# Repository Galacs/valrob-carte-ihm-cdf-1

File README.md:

# Carte IHM CDF 1

ESP32-S3-WROOM-1 HM interface card

## IC List

- ESP32-S3-WROOM-1 (Main MCU Module)
- TLV757P (MCU 3v3 LDO)
- SSD1315 (128x64 OLED display)
- 3x WS2812B (RGB status leds)
- 74HC14 (HEX Schmitt trigger)

## Top preview

## Preview 3d render

## Pin definitions

```c
#define DIP_A_PIN 14
#define DIP_B_PIN 21
#define DIP_C_PIN 47
#define DIP_D_PIN 48

#define STARTER_PIN 11

#define TEAM_A_PIN 13
#define TEAM_B_PIN 12

#define UP_BTN_PIN 10
#define DOWN_BTN_PIN 17
#define CONF_BTN_PIN 18

#define OLED_I2C_SCL 3
#define OLED_I2C_SDA 9

#define RBG_LEDS_PIN 45

#define BATT_SENSE_PIN 2
```

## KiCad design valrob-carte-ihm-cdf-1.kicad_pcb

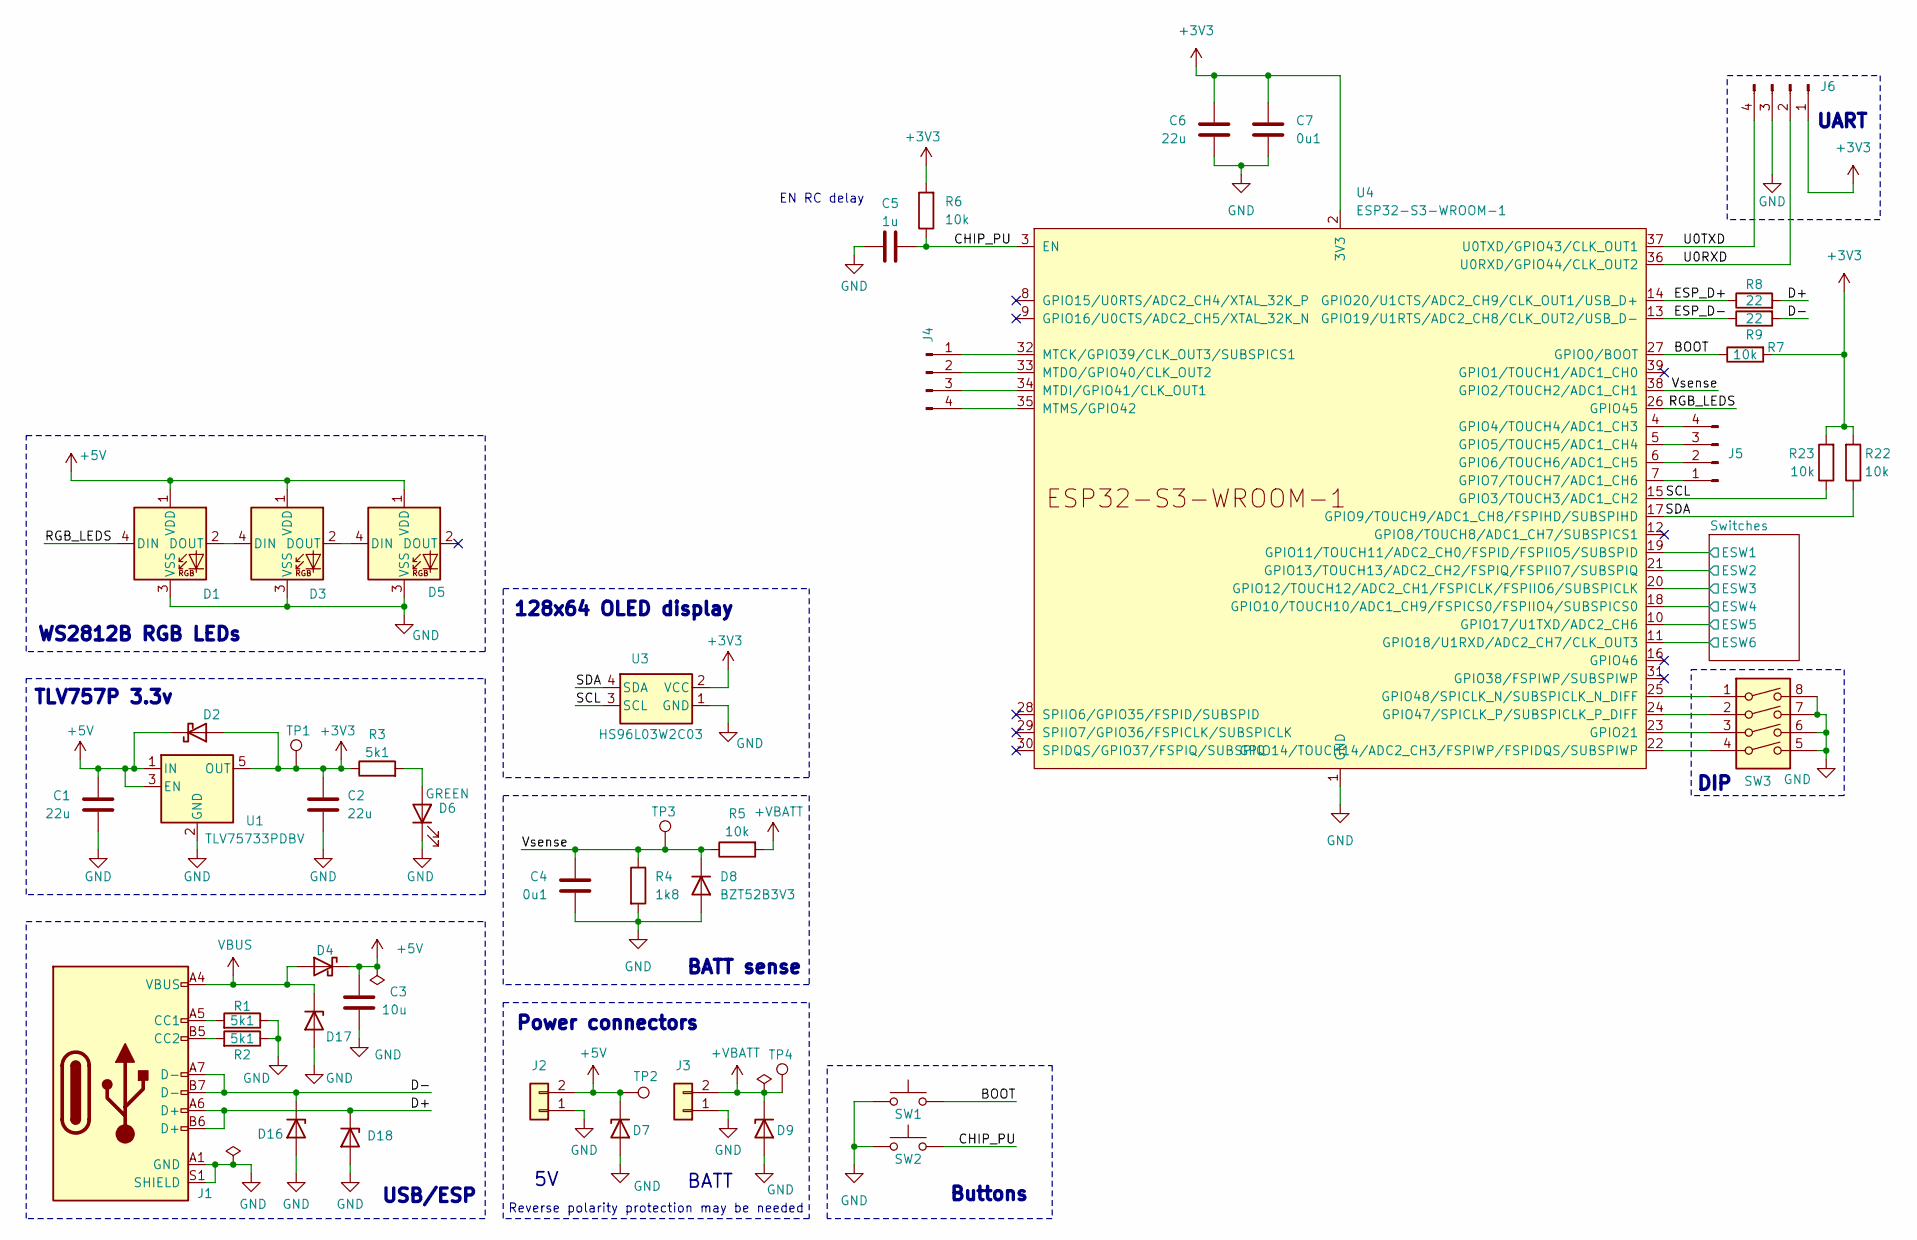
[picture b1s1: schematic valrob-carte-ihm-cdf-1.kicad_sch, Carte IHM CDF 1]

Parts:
C1, C2, C6: 22u; C_0603_1608Metric; Manufacturer Part Number CL10A226MQ8NRNC; JLCPCB Part # C59461
C3: 10u; C_0603_1608Metric; Manufacturer Part Number CL10A106KP8NNNC; JLCPCB Part # C19702
C4, C7: 0u1; C_0402_1005Metric; Manufacturer Part Number CL05B104KO5NNNC; JLCPCB Part # C1525
C5: 1u; C_0402_1005Metric; Manufacturer Part Number CL05A105KA5NQNC; JLCPCB Part # C52923
D1, D3, D5: WS2812B; LED_WS2812B_PLCC4_5.0x5.0mm_P3.2mm; Manufacturer Part Number WS2812B-HS01/W; JLCPCB Part # C22371521
D2, D4: D_Schottky; D_SMA; Manufacturer Part Number SS54; JLCPCB Part # C22452
D6: GREEN; LED_0805_2012Metric; Manufacturer Part Number KT-0805G; JLCPCB Part # C2297
D7: P6SMB6.8CA/TR13; D_SMB; Manufacturer Part Number P6SMB6.8CA/TR13; JLCPCB Part # C78395
D8: BZT52B3V3; D_SOD-123; Manufacturer Part Number BZT52B3V3; JLCPCB Part # C19077392
D9: SMAJ12A; D_SMA; Manufacturer Part Number SMAJ12A; JLCPCB Part # C19077531
D16, D17, D18: H5VU10U; Diode_DFN1006; Manufacturer Part Number H5VU10U; JLCPCB Part # C22395519
J1: USB_C_Receptacle_USB2.0_14P; USB_C_Receptacle_HRO_TYPE-C-31-M-12; Manufacturer Part Number TYPE-C16PIN; JLCPCB Part # C393939
J2, J3: Conn_01x02; JST_XH_S2B-XH-A_1x02_P2.50mm_Horizontal
J4, J5, J6: Conn_01x04_Pin; PinHeader_1x04_P2.54mm_Vertical
R1, R2, R3: 5k1; R_0402_1005Metric; Manufacturer Part Number 0402WGF5101TCE; JLCPCB Part # C25905
R4: 1k8; R_0603_1608Metric; Manufacturer Part Number 0603WAF1801T5E; JLCPCB Part # C4177
R5, R6, R7, R22, R23: 10k; R_0402_1005Metric; Manufacturer Part Number 0402WGF1002TCE; JLCPCB Part # C25744
R8, R9: 22; R_0402_1005Metric; Manufacturer Part Number 0402WGF220JTCE; JLCPCB Part # C25092
SW1, SW2: SW_Push; SW_SPST_TS-1088-xR020; Manufacturer Part Number TS-1088-AR02016; JLCPCB Part # C720477
SW3: SW_DIP_x04; SW_DIP_SPSTx04_Slide_9.78x12.34mm_W7.62mm_P2.54mm
TP1, TP2, TP3, TP4: TestPoint; TestPoint_Pad_D2.0mm
U1: TLV75733PDBV; SOT-23-5; Manufacturer Part Number TLV75733PDBVR; JLCPCB Part # C485517
U3: HS96L03W2C03
U4: ESP32-S3-WROOM-1

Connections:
+3V3: C2.2, C6.1, C7.1, D2.2 (A), J6.1, R3.1, R6.2, R7.2, R22.2, R23.2, TP1.1, U1.5 (OUT), U3.2 (VCC), U4.2 (3V3); also elsewhere on the board
+5V: C1.2, C3.1, D1.1 (VDD), D2.1 (K), D3.1 (VDD), D4.1 (K), D5.1 (VDD), D7.1 (K), J2.2, TP2.1, U1.1 (IN), U1.3 (EN)
+VBATT: D9.1 (K), J3.2, R5.2, TP4.1
/BOOT: R7.1, SW1.2, U4.27 (GPIO0/BOOT)
/CHIP_PU: C5.2, R6.1, SW2.2, U4.3 (EN)
/D+: D18.1 (K), J1.A6 (D+), J1.B6 (D+), R8.2
/D-: D16.1 (K), J1.A7 (D-), J1.B7 (D-), R9.2
/ESP_D+: R8.1, U4.14 (GPIO20/U1CTS/ADC2_CH9/CLK_OUT1/USB_D+)
/ESP_D-: R9.1, U4.13 (GPIO19/U1RTS/ADC2_CH8/CLK_OUT2/USB_D-)
/RGB_LEDS: D1.4 (DIN), U4.26 (GPIO45)
/SCL: R23.1, U3.3 (SCL), U4.15 (GPIO3/TOUCH3/ADC1_CH2)
/SDA: R22.1, U3.4 (SDA), U4.17 (GPIO9/TOUCH9/ADC1_CH8/FSPIHD/SUBSPIHD)
/Switches/ESW1: U4.19 (GPIO11/TOUCH11/ADC2_CH0/FSPID/FSPIIO5/S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); also elsewhere on the board
/Switches/ESW2: U4.21 (GPIO13/TOUCH13/ADC2_CH2/FSPIQ/FSPIIO7/S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); also elsewhere on the board
/Switches/ESW3: U4.20 (GPIO12/TOUCH12/ADC2_CH1/FSPICLK/FSPIIO6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); also elsewhere on the board
/Switches/ESW4: U4.18 (GPIO10/TOUCH10/ADC1_CH9/FSPICS0/FSPIIO4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); also elsewhere on the board
/Switches/ESW5: U4.10 (GPIO17/U1TXD/ADC2_CH6); also elsewhere on the board
/Switches/ESW6: U4.11 (GPIO18/U1RXD/ADC2_CH7/CLK_OUT3); also elsewhere on the board
/U0RXD: J6.2, U4.36 (U0RXD/GPIO44/CLK_OUT2)
/U0TXD: J6.4, U4.37 (U0TXD/GPIO43/CLK_OUT1)
/Vsense: C4.1, D8.1 (K), R4.1, R5.1, TP3.1, U4.38 (GPIO2/TOUCH2/ADC1_CH1)
GND: C1.1, C2.1, C3.2, C4.2, C5.1, C6.2, C7.2, D1.3 (VSS), D3.3 (VSS), D5.3 (VSS), D6.1 (K), D7.2 (A), D8.2 (A), D9.2 (A), D16.2 (A), D17.2 (A), D18.2 (A), J1.A1 (GND), J1.A12 (GND), J1.B1 (GND), J1.B12 (GND), J1.S1 (SHIELD), J2.1, J3.1, J6.3, R1.1, R2.1, R4.2, SW1.1, SW2.1, SW3.5, SW3.6, SW3.7, SW3.8, U1.2 (GND), U3.1 (GND), U4.1 (GND), U4.40 (GND), U4.41 (GND); also elsewhere on the board
unnamed: D1.2 (DOUT), D3.4 (DIN)
unnamed: D3.2 (DOUT), D5.4 (DIN)
unnamed: D6.2 (A), R3.2
unnamed: J1.A5 (CC1), R1.2
unnamed: J1.B5 (CC2), R2.2
unnamed: J4.1, U4.32 (MTCK/GPIO39/CLK_OUT3/SUBSPICS1)
unnamed: J4.2, U4.33 (MTDO/GPIO40/CLK_OUT2)
unnamed: J4.3, U4.34 (MTDI/GPIO41/CLK_OUT1)
unnamed: J4.4, U4.35 (MTMS/GPIO42)
unnamed: J5.1, U4.7 (GPIO7/TOUCH7/ADC1_CH6)
unnamed: J5.2, U4.6 (GPIO6/TOUCH6/ADC1_CH5)
unnamed: J5.3, U4.5 (GPIO5/TOUCH5/ADC1_CH4)
unnamed: J5.4, U4.4 (GPIO4/TOUCH4/ADC1_CH3)
unnamed: SW3.4, U4.22 (GPIO14/TOUCH14/ADC2_CH3/FSPIWP/FSPIDQS/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)
unnamed: SW3.3, U4.23 (GPIO21)
unnamed: SW3.2, U4.24 (GPIO47/SPICLK_P/SUBSPICLK_P_DIFF)
unnamed: SW3.1, U4.25 (GPIO48/SPICLK_N/SUBSPICLK_N_DIFF)
VBUS: D4.2 (A), D17.1 (K), J1.A4 (VBUS), J1.A9 (VBUS), J1.B4 (VBUS), J1.B9 (VBUS)

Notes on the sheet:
TLV757P 3.3v
Buttons
WS2812B RGB LEDs
Power connectors
DIP
EN RC delay
USB/ESP
BATT sense
UART
Reverse polarity protection may be needed
BATT
128x64 OLED display

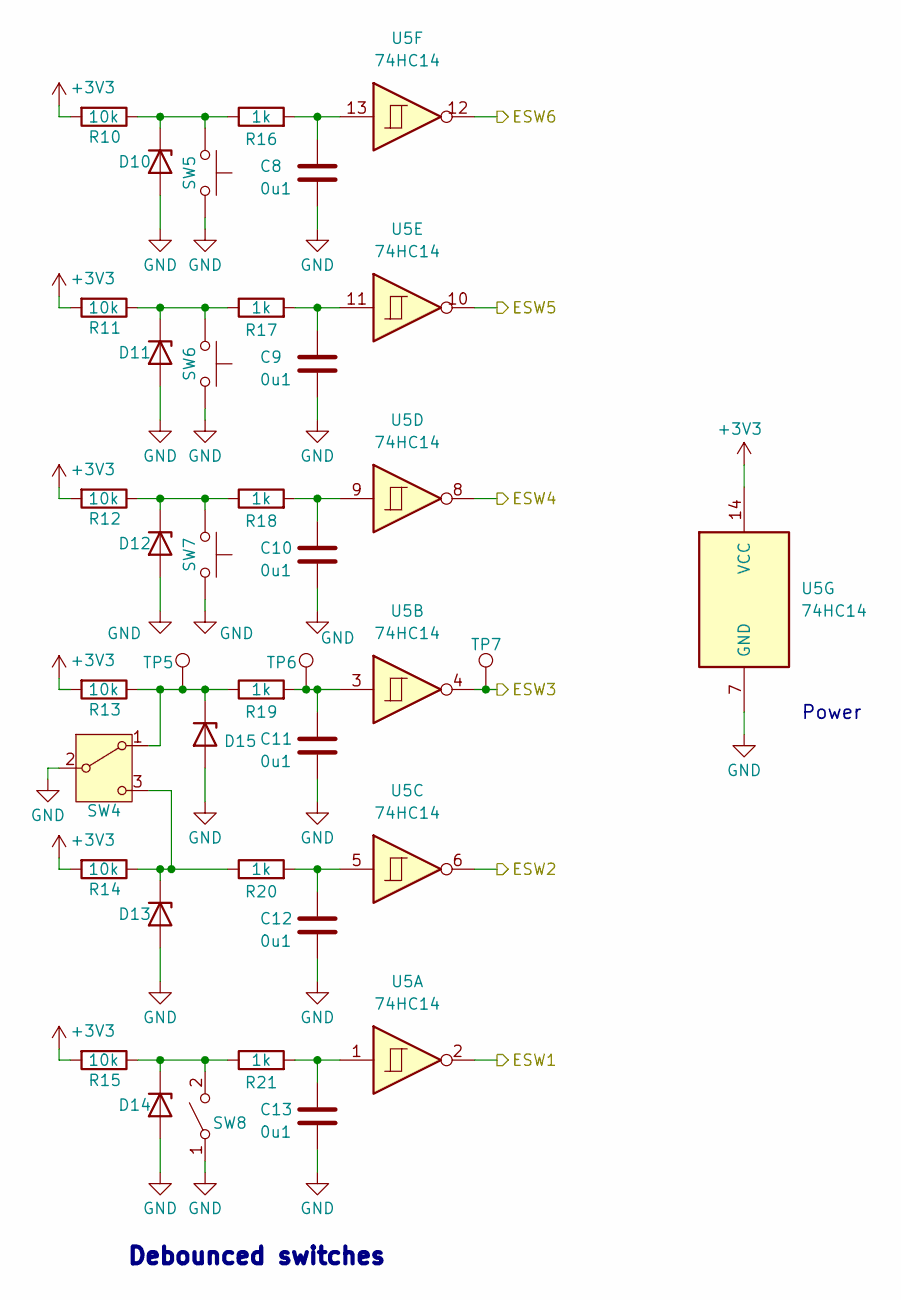
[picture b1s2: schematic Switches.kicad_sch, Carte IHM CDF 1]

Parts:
C8, C9, C10, C11, C12, C13: 0u1; C_0402_1005Metric; Manufacturer Part Number CL05B104KO5NNNC; JLCPCB Part # C1525
D10, D11, D12, D13, D14, D15: H5VU10U; Diode_DFN1006; Manufacturer Part Number H5VU10U; JLCPCB Part # C22395519
R10, R11, R12, R13, R14, R15: 10k; R_0402_1005Metric; Manufacturer Part Number 0402WGF1002TCE; JLCPCB Part # C25744
R16, R17, R18, R19, R20, R21: 1k; R_0402_1005Metric; Manufacturer Part Number 0402WGF1001TCE; JLCPCB Part # C11702
SW4: SW_SPDT; MT-0-102-A101-M200-RS
SW5, SW6, SW7: SW_Push; SW_PUSH_6mm_H7.3mm
SW8: SW_SPST; PinHeader_1x02_P2.54mm_Vertical
TP5, TP6, TP7: TestPoint; TestPoint_Pad_D2.0mm
U5: 74HC14; SOIC-14_3.9x8.7mm_P1.27mm; Manufacturer Part Number 74HC14D,653; JLCPCB Part # C5605

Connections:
+3V3: R10.2, R11.2, R12.2, R13.2, R14.2, R15.2, U5.14 (VCC); also elsewhere on the board
/Switches/ESW1: U5.2; also elsewhere on the board
/Switches/ESW2: U5.6; also elsewhere on the board
/Switches/ESW3: TP7.1, U5.4; also elsewhere on the board
/Switches/ESW4: U5.8; also elsewhere on the board
/Switches/ESW5: U5.10; also elsewhere on the board
/Switches/ESW6: U5.12; also elsewhere on the board
GND: C8.2, C9.2, C10.2, C11.2, C12.2, C13.2, D10.2 (A), D11.2 (A), D12.2 (A), D13.2 (A), D14.2 (A), D15.2 (A), SW4.2 (B), SW5.1, SW6.1, SW7.1, SW8.1 (A), U5.7 (GND); also elsewhere on the board
unnamed: C8.1, R16.2, U5.13
unnamed: C9.1, R17.2, U5.11
unnamed: C10.1, R18.2, U5.9
unnamed: C11.1, R19.2, TP6.1, U5.3
unnamed: C12.1, R20.2, U5.5
unnamed: C13.1, R21.2, U5.1
unnamed: D10.1 (K), R10.1, R16.1, SW5.2
unnamed: D11.1 (K), R11.1, R17.1, SW6.2
unnamed: D12.1 (K), R12.1, R18.1, SW7.2
unnamed: D13.1 (K), R14.1, R20.1, SW4.3 (C)
unnamed: D14.1 (K), R15.1, R21.1, SW8.2 (B)
unnamed: D15.1 (K), R13.1, R19.1, SW4.1 (A), TP5.1

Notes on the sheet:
Debounced switches
Power

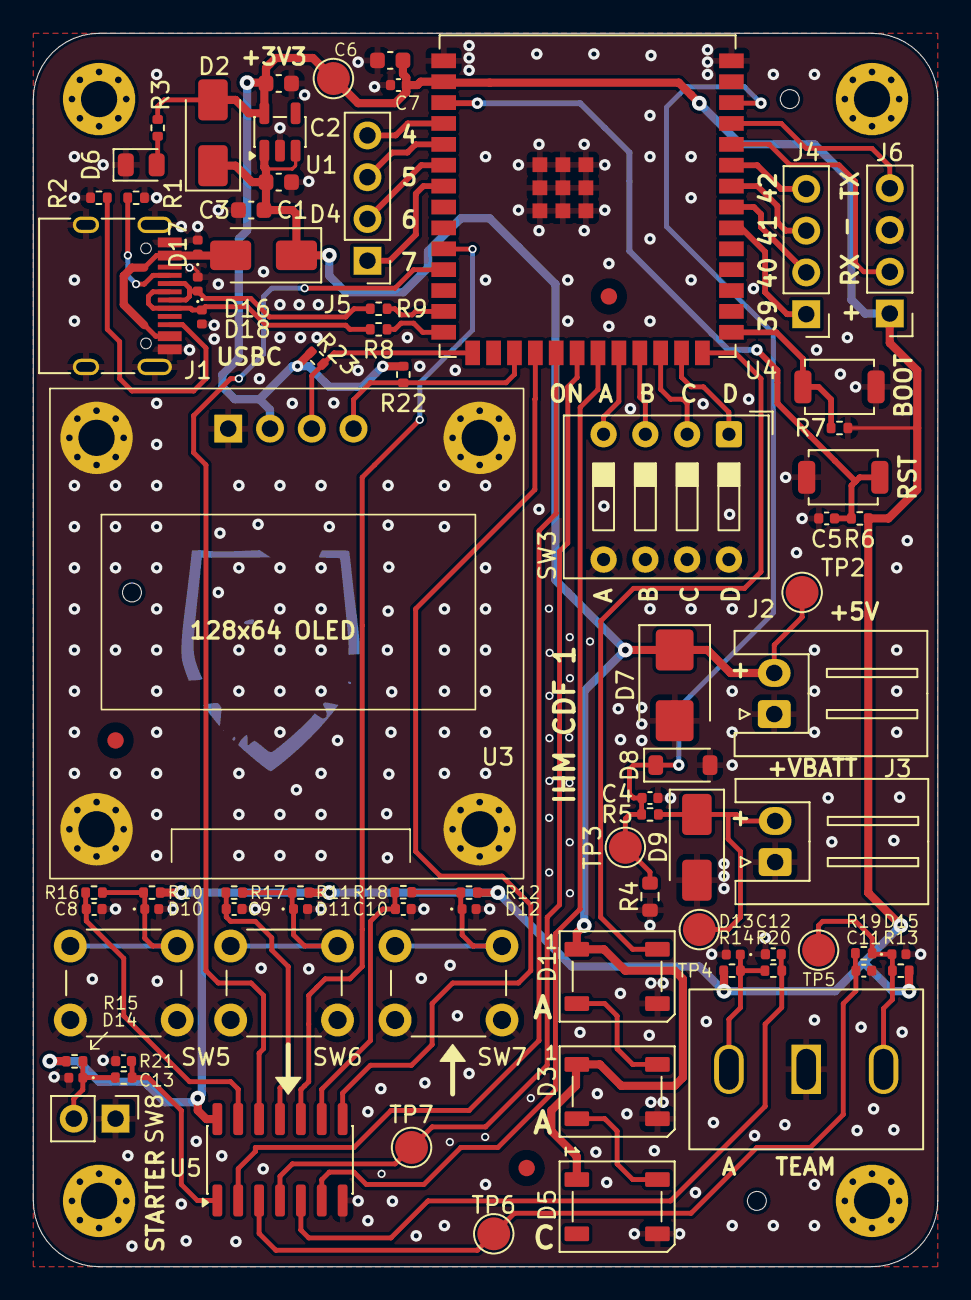
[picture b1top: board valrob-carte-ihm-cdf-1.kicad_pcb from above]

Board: 2 copper layers, 55.0 x 75.0 mm, 79 parts (0 on the bottom side), 52 nets.

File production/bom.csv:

Designator,Footprint,Quantity,Value,LCSC Part #
"C1, C2, C6",0603,3,22u,C59461
"C10, C11, C12, C13, C4, C7, C8, C9",0402,8,0u1,C1525
C3,0603,1,10u,C19702
C5,0402,1,1u,C52923
"D1, D3, D5",LED_WS2812B_PLCC4_5.0x5.0mm_P3.2mm,3,WS2812B,C22371521
"D10, D11, D12, D13, D14, D15, D16, D17, D18",Diode_DFN1006,9,H5VU10U,C22395519
"D2, D4",D_SMA,2,D_Schottky,C22452
D6,0805,1,GREEN,C2297
D7,D_SMB,1,P6SMB6.8CA/TR13,C78395
D8,D_SOD-123,1,BZT52B3V3,C19077392
D9,D_SMA,1,SMAJ12A,C19077531
J1,USB_C_Receptacle_HRO_TYPE-C-31-M-12,1,USB_C_Receptacle_USB2.0_14P,C393939
"R1, R2, R3",0402,3,5k1,C25905
"R10, R11, R12, R13, R14, R15, R22, R23, R5, R6, R7",0402,11,10k,C25744
"R16, R17, R18, R19, R20, R21",0402,6,1k,C11702
R4,0603,1,1k8,C4177
"R8, R9",0402,2,22,C25092
"SW1, SW2",SW_SPST_TS-1088-xR020,2,SW_Push,C720477
U1,SOT-23-5,1,TLV75733PDBV,C485517
U5,SOIC-14_3.9x8.7mm_P1.27mm,1,74HC14,C5605

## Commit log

2025-11-24 schem: import ESP32-S3-WROOM-1 from valrob-carte-moteur-cdf-1
2025-11-24 schem: import USBC from valrob-carte-moteur-cdf-1
2025-11-24 schem: add TLV757P 3.3v LDO
2025-11-24 schem: import BOOT and RST buttons from valrob-carte-moteur-cdf-1
2025-11-24 schem: add VBATT voltage sense
2025-11-24 schem: add dip switches
2025-11-24 schem: add debounced switches
2025-11-24 schem: add WS2812B addressable RGB LEDs
2025-11-24 schem: add HS96L03W2C03 OLED display
2025-11-24 schem: add spare GPIOs
2025-11-24 schem: add switches footprints
2025-11-24 schem: add test points
2025-11-24 schem: add no connects
2025-11-24 schem: connect i2c to MCU
2025-11-24 schem: run and fix ERC
2025-11-24 schem: add net class assignements
2025-11-24 schem: add title
2025-11-24 schem: reannotate
2025-11-24 schem: assign footprints
2025-11-24 schem: add part numbers to BOM
2025-11-24 pcb: create file and import stackup
2025-11-24 pcb: import components from schematic
2025-11-24 pcb: add missing 3d models
2025-11-24 pcb: add initial rough placement
2025-11-24 pcb: add layout refinement and board outline
2025-11-24 pcb: add M2 mounting holes
2025-11-24 pcb: add fiducials and tooling holes
2025-11-24 pcb: refine layout
2025-11-24 pcb: add ground planes
2025-11-24 pcb: add gnd vias
2025-11-24 pcb: place grid and drill origin
2025-11-24 pcb: add USB routing
2025-11-24 pcb: add UART routing
2025-11-24 pcb: add I2C display routing
2025-11-24 pcb: add display buttons routing
2025-11-24 pcb: add toggle switch routing
2025-11-24 pcb: add DIP switches routing
2025-11-24 pcb: add RGB leds routing
2025-11-24 pcb: add spare GPIO routing
2025-11-24 pcb: add 3V3 power routing
2025-11-24 pcb: add 5V power routing
2025-11-24 pcb: add RST and BOOT btns routing
2025-11-24 pcb(silkscreen): clean up reference designators
2025-11-24 pcb: add stitching vias
2025-11-24 pcb(silkscreen): add company logo
2025-11-25 switch ST usb ESD to H5VU10U tvs diodes
2025-11-25 pcb(silkscreen): improve user txt
2025-11-25 pcb(silkscreen): refine
2025-11-25 pcb: add title
2025-11-25 add production files
2025-11-30 regenerate production files
2025-12-01 pcb/schem: add missing i2c external pullups
2025-12-05 add README.md
2025-12-05 docs: add pin definitions to readme
2025-12-11 docs: add preview images to README
2025-12-18 pcb/schem: fix BOOT pullup
